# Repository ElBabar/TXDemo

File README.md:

# TXDemo
Demo board for CAN and XBee communication

Developped for a UTT course.

This board has onboard CAN communication and fits a XBee adapter (see XBeeSX868_adapter) in order to communicate with both, using a homemade protocol.

This board is a demo board for functions that will be implemented on a robot taking part in the Coupe de france de Robotique.

You might need to use my library:
add https://github.com/ElBabar/Libabar.git
to your KiCad paths.

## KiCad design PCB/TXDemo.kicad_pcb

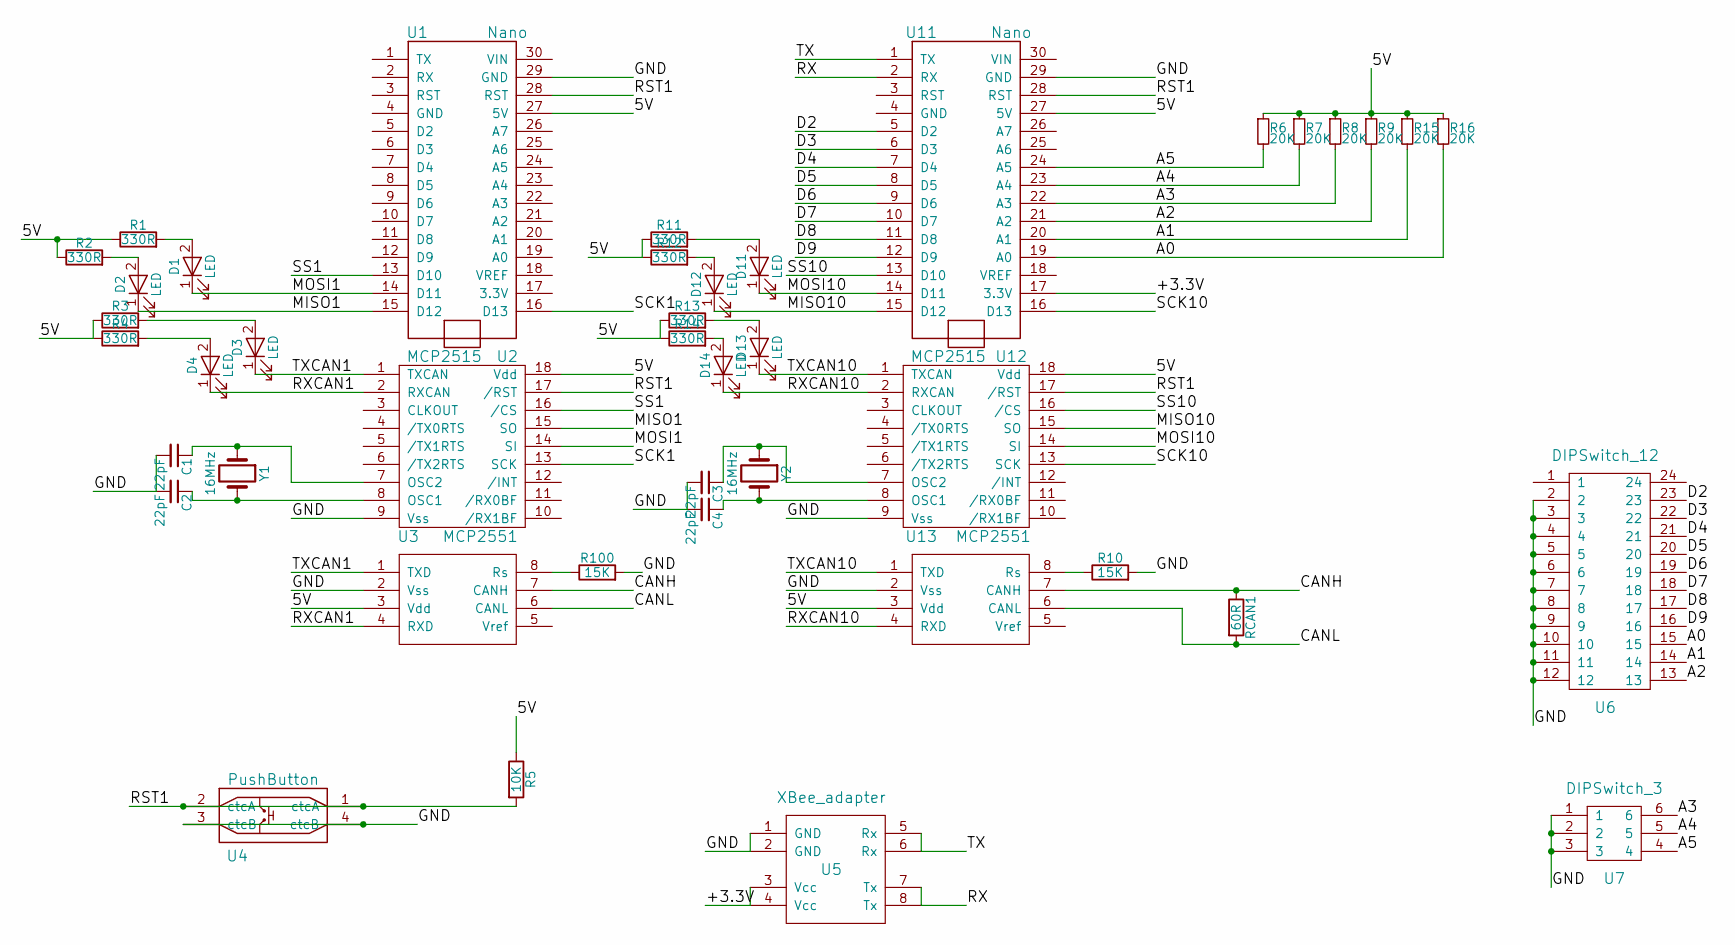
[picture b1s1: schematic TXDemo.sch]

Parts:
C1, C2, C3, C4: 22pF; C_0805_HandSoldering
D1, D2, D3, D4, D11, D12, D13, D14: LED; LED_0603_HandSoldering
R1, R2, R3, R4, R11, R12, R13, R14: 330R; R_0805_HandSoldering
R5: 10K; R_0805_HandSoldering
R6, R7, R8, R9, R15, R16: 20K; R_0805_HandSoldering
R10, R100: 15K; R_0805_HandSoldering
RCAN1: 60R; R_Axial_DIN0207_L6.3mm_D2.5mm_P10.16mm_Horizontal
U1, U11: Nano
U2, U12: MCP2515; DIP-18_W7.62mm
U3, U13: MCP2551; DIP-8_W7.62mm
U4: PushButton
U5: XBee_adapter
U6: DIPSwitch_12
U7: DIPSwitch_3
Y1, Y2: 16MHz; Resonator-2pin_w10.0mm_h5.0mm

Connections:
/5V: R1.1, R2.1, R3.1, R4.1, R5.1, R6.1, R7.1, R8.1, R9.1, R11.1, R12.1, R13.1, R14.1, R15.1, R16.1, U1.27 (5V), U2.18 (Vdd), U3.3 (Vdd), U11.27 (5V), U12.18 (Vdd), U13.3 (Vdd)
/+3.3V: U5.3 (Vcc), U5.4 (Vcc), U11.17 (3.3V)
/A0: R16.2, U6.15, U11.19 (A0)
/A1: R15.2, U6.14, U11.20 (A1)
/A2: R9.2, U6.13, U11.21 (A2)
/A3: R8.2, U7.6, U11.22 (A3)
/A4: R7.2, U7.5, U11.23 (A4)
/A5: R6.2, U7.4, U11.24 (A5)
/CANH: RCAN1.1, U3.7 (CANH), U13.7 (CANH)
/CANL: RCAN1.2, U3.6 (CANL), U13.6 (CANL)
/D2: U6.23, U11.5 (D2)
/D3: U6.22, U11.6 (D3)
/D4: U6.21, U11.7 (D4)
/D5: U6.20, U11.8 (D5)
/D6: U6.19, U11.9 (D6)
/D7: U6.18, U11.10 (D7)
/D8: U6.17, U11.11 (D8)
/D9: U6.16, U11.12 (D9)
/GND: C1.2, C2.2, C3.2, C4.2, R10.2, R100.2, U1.29 (GND), U2.9 (Vss), U3.2 (Vss), U4.3 (ctcB), U4.4 (ctcB), U5.1 (GND), U5.2 (GND), U6.2, U6.3, U6.4, U6.5, U6.6, U6.7, U6.8, U6.9, U6.10, U6.11, U6.12, U7.1, U7.2, U7.3, U11.29 (GND), U12.9 (Vss), U13.2 (Vss)
/MISO1: D2.1 (K), U1.15 (D12), U2.15 (SO)
/MISO10: D12.1 (K), U11.15 (D12), U12.15 (SO)
/MOSI1: D1.1 (K), U1.14 (D11), U2.14 (SI)
/MOSI10: D11.1 (K), U11.14 (D11), U12.14 (SI)
/RST1: R5.2, U1.28 (RST), U2.17 (/RST), U4.1 (ctcA), U4.2 (ctcA), U11.28 (RST), U12.17 (/RST)
/RX: U5.7 (Tx), U5.8 (Tx), U11.2 (RX)
/RXCAN1: D4.1 (K), U2.2 (RXCAN), U3.4 (RXD)
/RXCAN10: D14.1 (K), U12.2 (RXCAN), U13.4 (RXD)
/SCK1: U1.16 (D13), U2.13 (SCK)
/SCK10: U11.16 (D13), U12.13 (SCK)
/SS1: U1.13 (D10), U2.16 (/CS)
/SS10: U11.13 (D10), U12.16 (/CS)
/TX: U5.5 (Rx), U5.6 (Rx), U11.1 (TX)
/TXCAN1: D3.1 (K), U2.1 (TXCAN), U3.1 (TXD)
/TXCAN10: D13.1 (K), U12.1 (TXCAN), U13.1 (TXD)
unnamed: C1.1, U2.7 (OSC2), Y1.1
unnamed: C2.1, U2.8 (OSC1), Y1.2
unnamed: C3.1, U12.7 (OSC2), Y2.1
unnamed: C4.1, U12.8 (OSC1), Y2.2
unnamed: D1.2 (A), R1.2
unnamed: D2.2 (A), R2.2
unnamed: D3.2 (A), R3.2
unnamed: D4.2 (A), R4.2
unnamed: D11.2 (A), R11.2
unnamed: D12.2 (A), R12.2
unnamed: D13.2 (A), R13.2
unnamed: D14.2 (A), R14.2
unnamed: R10.1, U13.8 (Rs)
unnamed: R100.1, U3.8 (Rs)

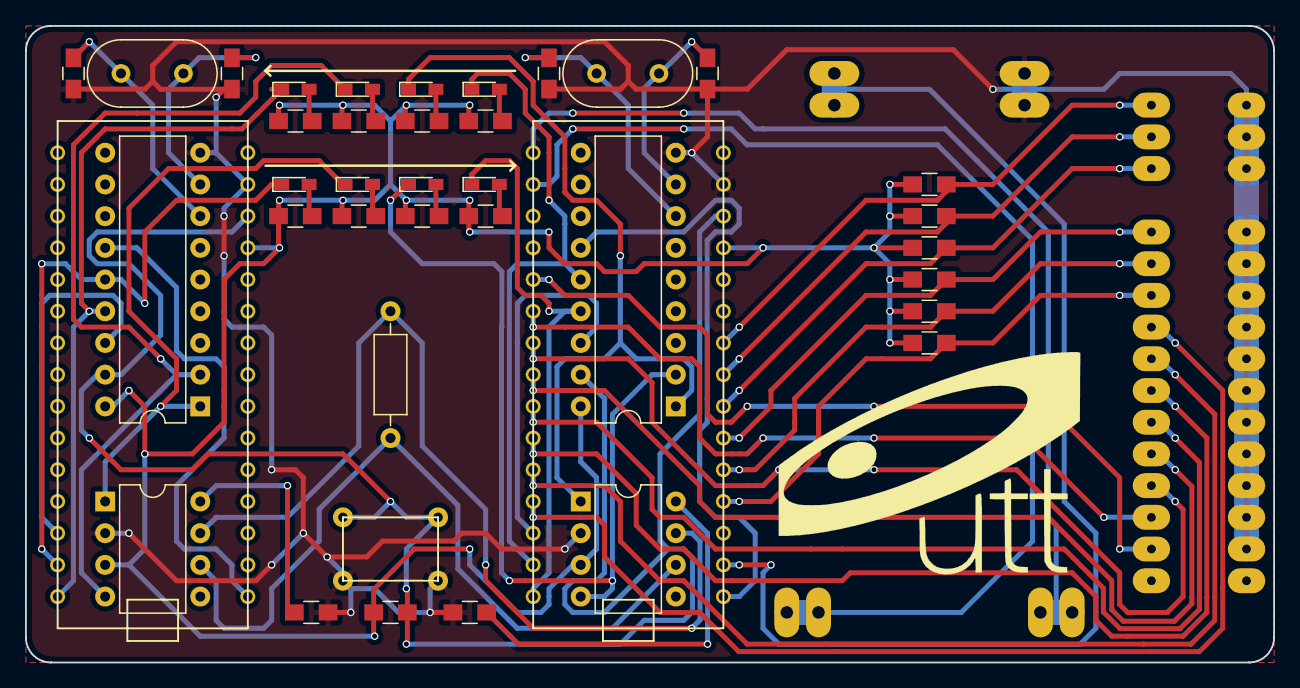
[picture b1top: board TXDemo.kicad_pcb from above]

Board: 2 copper layers, 100.0 x 51.0 mm, 42 parts (0 on the bottom side), 48 nets.

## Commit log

2017-12-08 Changed tree
2017-12-08 Moved Readme
